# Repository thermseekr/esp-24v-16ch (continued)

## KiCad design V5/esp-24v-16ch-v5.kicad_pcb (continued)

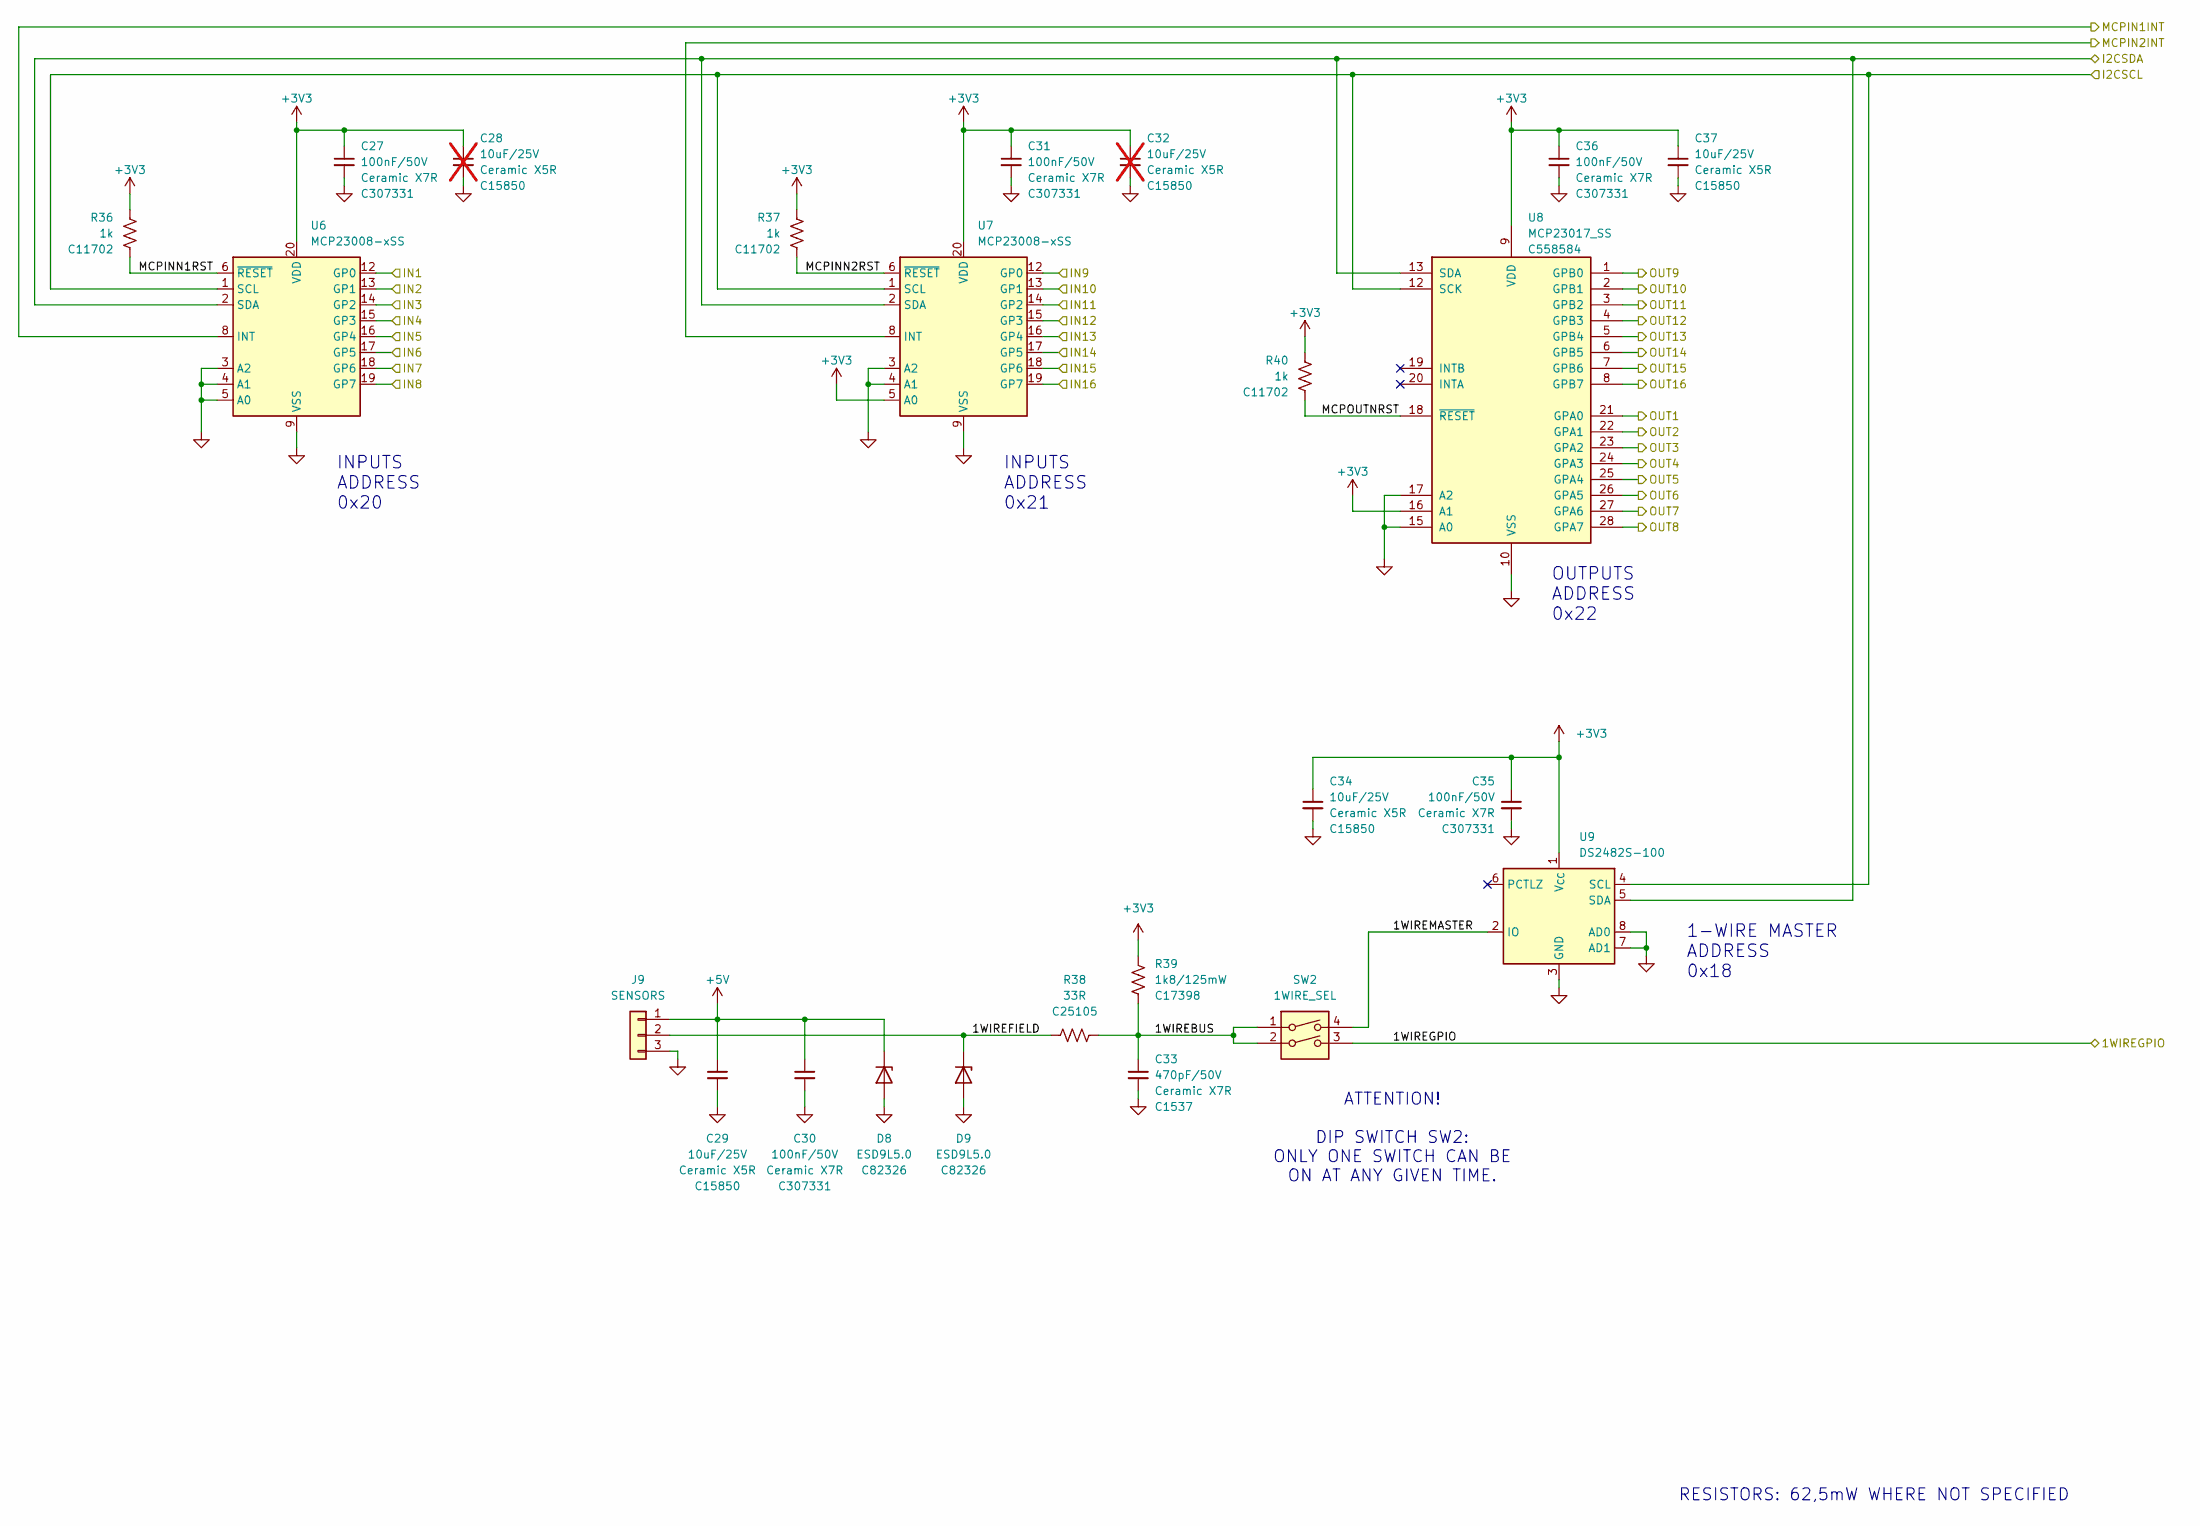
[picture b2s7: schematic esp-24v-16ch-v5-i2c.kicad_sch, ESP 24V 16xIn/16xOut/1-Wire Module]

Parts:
C27, C30, C31, C35, C36: 100nF/50V; C_0402_1005Metric; Mfr PN CL05B104KB54PNC; JLCPCB BOM 1
C28, C32: 10uF/25V; C_0805_2012Metric; Mfr PN CL21A106KAYNNNE; JLCPCB BOM 1; not fitted
C29, C34, C37: 10uF/25V; C_0805_2012Metric; Mfr PN CL21A106KAYNNNE; JLCPCB BOM 1
C33: 470pF/50V; C_0402_1005Metric; Mfr PN 0402B471K500NT; JLCPCB BOM 1
D8, D9: ESD9L5.0; D_SOD-923; Mfr PN ESD9L5.0ST5G; JLCPCB BOM 1
J9: SENSORS; TerminalBlock_Dibo_DB141V-2.54-3P_1x03_P2.54mm_Vertical; Mfr PN DB141V-2.54-3P-GN; JLCPCB BOM 1
R36, R37, R40: 1k; R_0402_1005Metric; Mfr PN 0402WGF1001TCE; LCSC Part # C11702
R38: 33R; R_0402_1005Metric; Mfr PN 0402WGF330JTCE; LCSC Part # C25105
R39: 1k8/125mW; R_0805_2012Metric; Mfr PN 0805W8F1801T5E; LCSC Part # C17398
SW2: 1WIRE_SEL; SW_DIP_SPSTx02_Slide_Copal_CHS-02B_W7.62mm_P1.27mm; Mfr PN DSHP02TS-S; JLCPCB BOM 1
U6, U7: MCP23008-xSS; SSOP-20_5.3x7.2mm_P0.65mm
U8: MCP23017_SS; SSOP-28_5.3x10.2mm_P0.65mm; Mfr PN MCP23017T-E/SS; JLCPCB BOM 1
U9: DS2482S-100; SO-8_3.9x4.9mm_P1.27mm; Mfr PN DS2482S-100; JLCPCB BOM 1

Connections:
+3V3: C27.1, C28.1, C31.1, C32.1, C34.1, C35.1, C36.1, C37.1, R36.1, R37.1, R39.1, R40.1, U6.20 (VDD), U7.5 (A0), U7.20 (VDD), U8.9 (VDD), U8.16 (A1), U9.1 (V_{CC}); also elsewhere on the board
+5V: C29.1, C30.1, D8.1 (K), J9.1; also elsewhere on the board
/I2C Devices/1WIREBUS: C33.1, R38.2, R39.2, SW2.1, SW2.2
/I2C Devices/1WIREFIELD: D9.1 (K), J9.2, R38.1
/I2C Devices/1WIREGPIO: SW2.3; also elsewhere on the board
/I2C Devices/1WIREMASTER: SW2.4, U9.2 (IO)
/I2C Devices/I2CSCL: U6.1 (SCL), U7.1 (SCL), U8.12 (SCK), U9.4 (SCL); also elsewhere on the board
/I2C Devices/I2CSDA: U6.2 (SDA), U7.2 (SDA), U8.13 (SDA), U9.5 (SDA); also elsewhere on the board
/I2C Devices/MCPIN1INT: U6.8 (INT); also elsewhere on the board
/I2C Devices/MCPIN2INT: U7.8 (INT); also elsewhere on the board
/I2C Devices/MCPINN1RST: R36.2, U6.6 (~RESET)
/I2C Devices/MCPINN2RST: R37.2, U7.6 (~RESET)
/I2C Devices/MCPOUTNRST: R40.2, U8.18 (~RESET)
/INPUT1: U6.12 (GP0); also elsewhere on the board
/INPUT2: U6.13 (GP1); also elsewhere on the board
/INPUT3: U6.14 (GP2); also elsewhere on the board
/INPUT4: U6.15 (GP3); also elsewhere on the board
/INPUT5: U6.16 (GP4); also elsewhere on the board
/INPUT6: U6.17 (GP5); also elsewhere on the board
/INPUT7: U6.18 (GP6); also elsewhere on the board
/INPUT8: U6.19 (GP7); also elsewhere on the board
/INPUT9: U7.12 (GP0); also elsewhere on the board
/INPUT10: U7.13 (GP1); also elsewhere on the board
/INPUT11: U7.14 (GP2); also elsewhere on the board
/INPUT12: U7.15 (GP3); also elsewhere on the board
/INPUT13: U7.16 (GP4); also elsewhere on the board
/INPUT14: U7.17 (GP5); also elsewhere on the board
/INPUT15: U7.18 (GP6); also elsewhere on the board
/INPUT16: U7.19 (GP7); also elsewhere on the board
/OUTPUT1: U8.21 (GPA0); also elsewhere on the board
/OUTPUT2: U8.22 (GPA1); also elsewhere on the board
/OUTPUT3: U8.23 (GPA2); also elsewhere on the board
/OUTPUT4: U8.24 (GPA3); also elsewhere on the board
/OUTPUT5: U8.25 (GPA4); also elsewhere on the board
/OUTPUT6: U8.26 (GPA5); also elsewhere on the board
/OUTPUT7: U8.27 (GPA6); also elsewhere on the board
/OUTPUT8: U8.28 (GPA7); also elsewhere on the board
/OUTPUT9: U8.1 (GPB0); also elsewhere on the board
/OUTPUT10: U8.2 (GPB1); also elsewhere on the board
/OUTPUT11: U8.3 (GPB2); also elsewhere on the board
/OUTPUT12: U8.4 (GPB3); also elsewhere on the board
/OUTPUT13: U8.5 (GPB4); also elsewhere on the board
/OUTPUT14: U8.6 (GPB5); also elsewhere on the board
/OUTPUT15: U8.7 (GPB6); also elsewhere on the board
/OUTPUT16: U8.8 (GPB7); also elsewhere on the board
GND: C27.2, C28.2, C29.2, C30.2, C31.2, C32.2, C33.2, C34.2, C35.2, C36.2, C37.2, D8.2 (A), D9.2 (A), J9.3, U6.3 (A2), U6.4 (A1), U6.5 (A0), U6.9 (VSS), U7.3 (A2), U7.4 (A1), U7.9 (VSS), U8.10 (VSS), U8.15 (A0), U8.17 (A2), U9.3 (GND), U9.7 (AD1), U9.8 (AD0); also elsewhere on the board

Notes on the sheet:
OUTPUTS ADDRESS 0x22
INPUTS ADDRESS 0x20
RESISTORS: 62,5mW WHERE NOT SPECIFIED
1-WIRE MASTER ADDRESS 0x18
INPUTS ADDRESS 0x21
ATTENTION! DIP SWITCH SW2: ONLY ONE SWITCH CAN BE ON AT ANY GIVEN TIME.

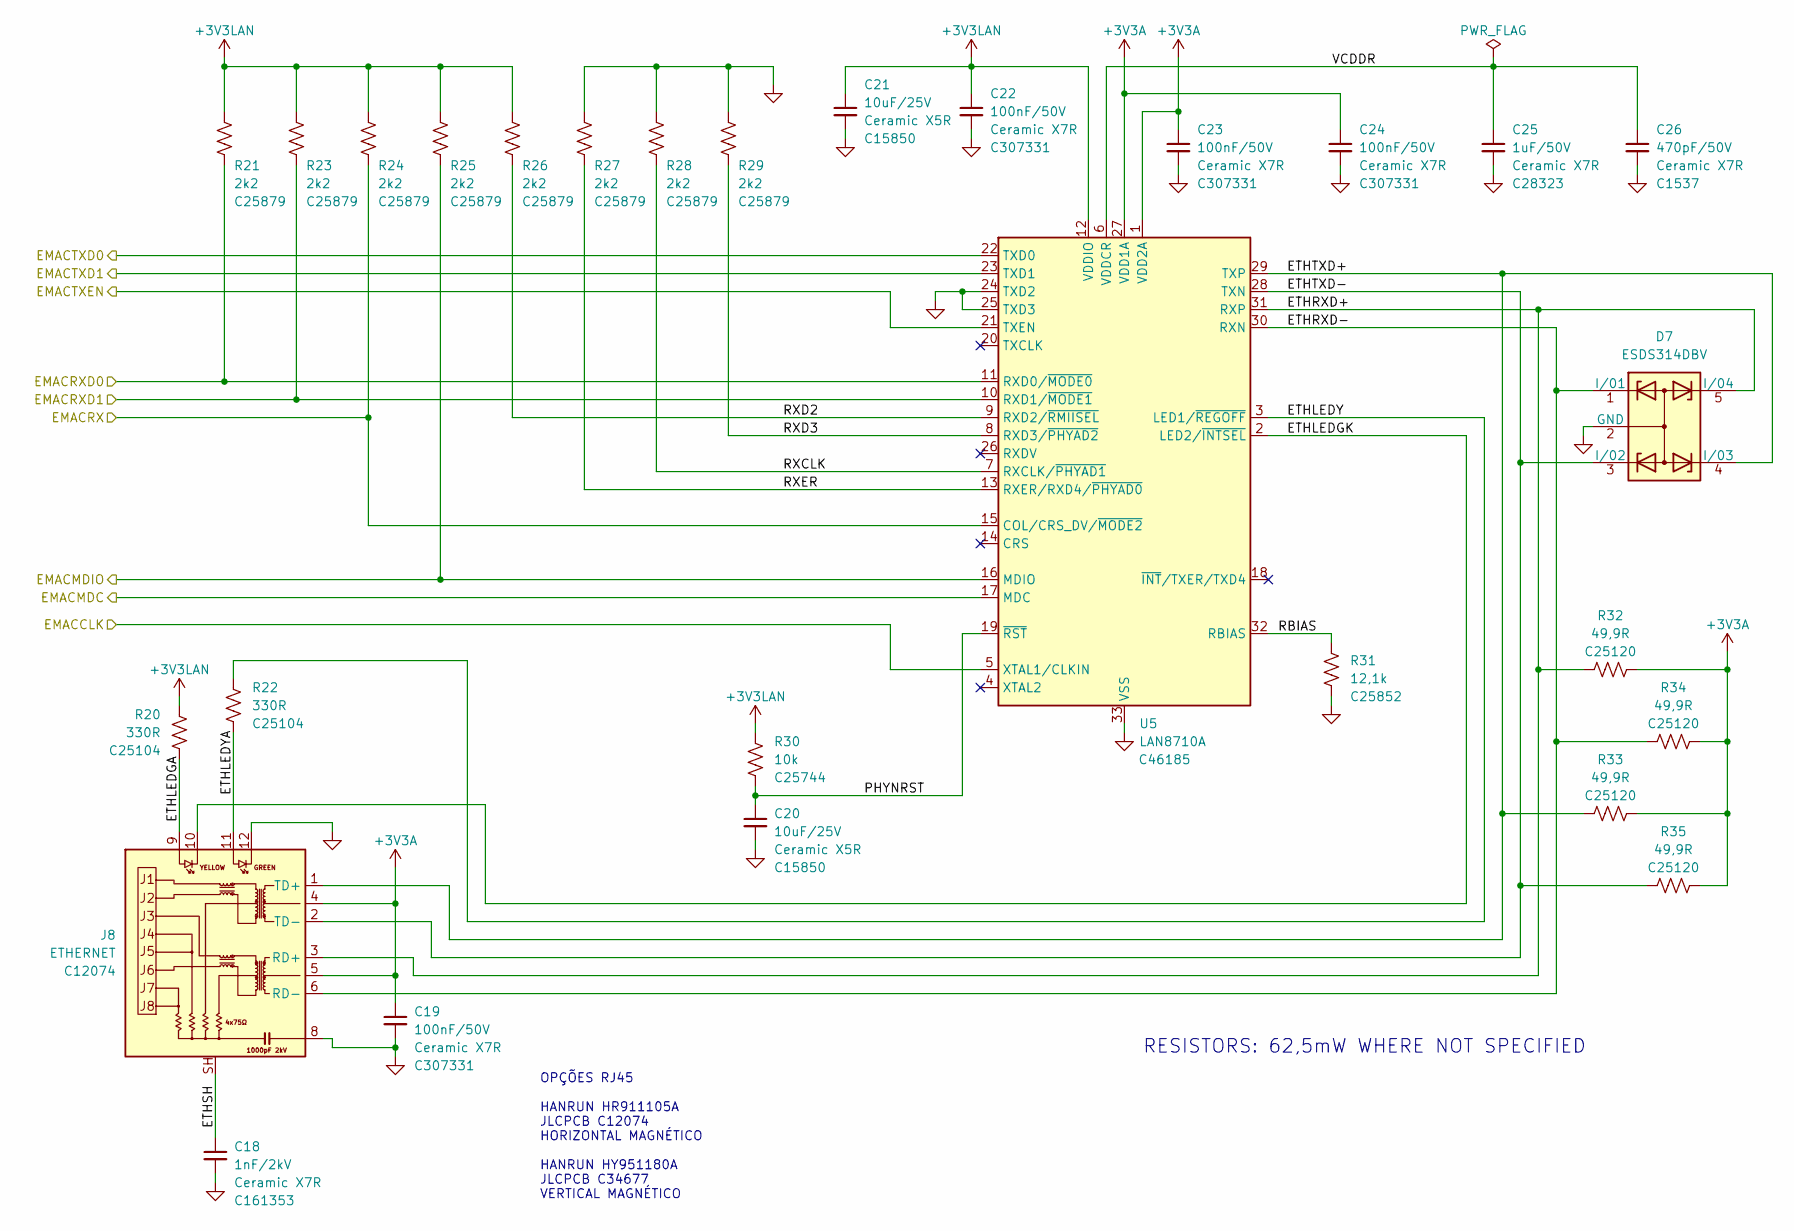
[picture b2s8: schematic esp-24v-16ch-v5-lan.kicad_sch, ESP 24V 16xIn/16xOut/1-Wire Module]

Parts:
C18: 1nF/2kV; C_1206_3216Metric; Mfr PN GR431BR7LA102KW66L; JLCPCB BOM 1
C19, C22, C23, C24: 100nF/50V; C_0402_1005Metric; Mfr PN CL05B104KB54PNC; JLCPCB BOM 1
C20, C21: 10uF/25V; C_0805_2012Metric; Mfr PN CL21A106KAYNNNE; JLCPCB BOM 1
C25: 1uF/50V; C_0805_2012Metric; Mfr PN CL21B105KBFNNNE; JLCPCB BOM 1
C26: 470pF/50V; C_0402_1005Metric; Mfr PN 0402B471K500NT; JLCPCB BOM 1
D7: ESDS314DBV; SOT-23-5; Mfr PN ESDS314DBVR; JLCPCB BOM 1
J8: ETHERNET; RJ45_HanRun_HR915340A; Mfr PN HR911105A; JLCPCB BOM 1
R20, R22: 330R; R_0402_1005Metric; Mfr PN 0402WGF3300TCE; LCSC Part # C25104
R21, R23, R24, R25, R26, R27, R28, R29: 2k2; R_0402_1005Metric; Mfr PN 0402WGF2201TCE; LCSC Part # C25879
R30: 10k; R_0402_1005Metric; Mfr PN 0402WGF1002TCE; LCSC Part # C25744
R31: 12,1k; R_0402_1005Metric; Mfr PN 0402WGF1212TCE; JLCPCB BOM 1
R32, R33, R34, R35: 49,9R; R_0402_1005Metric; Mfr PN 0402WGF499JTCE; JLCPCB BOM 1
U5: LAN8710A; QFN-32-1EP_5x5mm_P0.5mm_EP3.3x3.3mm_ThermalVias; Mfr PN LAN8710A-EZC-TR; JLCPCB BOM 1

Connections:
+3V3A: C19.1, C23.1, C24.1, J8.4, J8.5, R32.2, R33.2, R34.2, R35.2, U5.1 (VDD2A), U5.27 (VDD1A); also elsewhere on the board
+3V3LAN: C21.1, C22.1, R20.1, R21.1, R23.1, R24.1, R25.1, R26.1, R30.2, U5.12 (VDDIO); also elsewhere on the board
/LAN/EMACCLK: U5.5 (XTAL1/CLKIN); also elsewhere on the board
/LAN/EMACMDC: U5.17 (MDC); also elsewhere on the board
/LAN/EMACMDIO: R25.2, U5.16 (MDIO); also elsewhere on the board
/LAN/EMACRX: R24.2, U5.15 (COL/CRS_DV/~MODE2); also elsewhere on the board
/LAN/EMACRXD0: R21.2, U5.11 (RXD0/~MODE0); also elsewhere on the board
/LAN/EMACRXD1: R23.2, U5.10 (RXD1/~MODE1); also elsewhere on the board
/LAN/EMACTXD0: U5.22 (TXD0); also elsewhere on the board
/LAN/EMACTXD1: U5.23 (TXD1); also elsewhere on the board
/LAN/EMACTXEN: U5.21 (TXEN); also elsewhere on the board
/LAN/ETHLEDGA: J8.9, R20.2
/LAN/ETHLEDGK: J8.10, U5.2 (LED2/~INTSEL)
/LAN/ETHLEDY: R22.1, U5.3 (LED1/~REGOFF)
/LAN/ETHLEDYA: J8.11, R22.2
/LAN/ETHRXD+: D7.5 (I/04), J8.3 (RD+), R32.1, U5.31 (RXP)
/LAN/ETHRXD-: D7.1 (I/01), J8.6 (RD-), R34.1, U5.30 (RXN)
/LAN/ETHSH: C18.1, J8.SH
/LAN/ETHTXD+: D7.4 (I/03), J8.1 (TD+), R33.1, U5.29 (TXP)
/LAN/ETHTXD-: D7.3 (I/02), J8.2 (TD-), R35.1, U5.28 (TXN)
/LAN/PHYNRST: C20.1, R30.1, U5.19 (~RST)
/LAN/RBIAS: R31.1, U5.32 (RBIAS)
/LAN/RXCLK: R28.2, U5.7 (RXCLK/~PHYAD1)
/LAN/RXD2: R26.2, U5.9 (RXD2/~RMIISEL)
/LAN/RXD3: R29.2, U5.8 (RXD3/~PHYAD2)
/LAN/RXER: R27.2, U5.13 (RXER/RXD4/~PHYAD0)
/LAN/VCDDR: C25.1, C26.1, U5.6 (VDDCR)
GND: C18.2, C19.2, C20.2, C21.2, C22.2, C23.2, C24.2, C25.2, C26.2, D7.2 (GND), J8.8, J8.12, R27.1, R28.1, R29.1, R31.2, U5.24 (TXD2), U5.25 (TXD3), U5.33 (VSS); also elsewhere on the board

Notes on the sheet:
OPÇÕES RJ45 HANRUN HR911105A JLCPCB C12074 HORIZONTAL MAGNÉTICO HANRUN HY951180A JLCPCB C34677 VERTICAL MAGNÉTICO
RESISTORS: 62,5mW WHERE NOT SPECIFIED

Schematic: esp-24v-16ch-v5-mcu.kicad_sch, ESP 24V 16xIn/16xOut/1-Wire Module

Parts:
C13, C16: 10uF/25V; C_0805_2012Metric; Mfr PN CL21A106KAYNNNE; JLCPCB BOM 1
C14, C17: 100nF/50V; C_0402_1005Metric; Mfr PN CL05B104KB54PNC; JLCPCB BOM 1
C15: 1uF/50V; C_0805_2012Metric; Mfr PN CL21B105KBFNNNE; JLCPCB BOM 1
Q3: UMH3N; SOT-363_SC-70-6; Mfr PN UMH3N; JLCPCB BOM 1
R12, R13, R18: 10k; R_0402_1005Metric; Mfr PN 0402WGF1002TCE; LCSC Part # C25744
R14: 33R; R_0402_1005Metric; Mfr PN 0402WGF330JTCE; LCSC Part # C25105
R15, R16, R17, R19: 2k2; R_0402_1005Metric; Mfr PN 0402WGF2201TCE; LCSC Part # C25879
SW1: RESET; SW_SPST_Xunpu_TS1088AR02016; Mfr PN TS-1088-AR02016; JLCPCB BOM 1
U3: CH340K; SSOP-10-1EP_3.9x4.9mm_P1mm_EP2.1x3.3mm; Mfr PN CH340K; JLCPCB BOM 1
U4: ESP32-WROOM-32UE-N16; ESP32-WROOM-32U; Mfr PN ESP32-WROOM-32UE-N16; JLCPCB BOM 1

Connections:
+3V3: C13.1, C14.1, C16.1, C17.1, R12.1, R13.1, R15.1, R16.1, R17.1, R19.1, U3.7 (VCC), U3.10 (V3), U4.2 (VDD); also elsewhere on the board
/I2C Devices/1WIREGPIO: U4.27 (IO16); also elsewhere on the board
/I2C Devices/I2CSCL: R17.2, U4.8 (IO32); also elsewhere on the board
/I2C Devices/I2CSDA: R19.2, U4.9 (IO33); also elsewhere on the board
/I2C Devices/MCPIN1INT: R15.2, U4.16 (IO13); also elsewhere on the board
/I2C Devices/MCPIN2INT: R16.2, U4.13 (IO14); also elsewhere on the board
/LAN/EMACCLK: R14.2; also elsewhere on the board
/LAN/EMACMDC: U4.37 (IO23); also elsewhere on the board
/LAN/EMACMDIO: U4.30 (IO18); also elsewhere on the board
/LAN/EMACRX: U4.12 (IO27); also elsewhere on the board
/LAN/EMACRXD0: U4.10 (IO25); also elsewhere on the board
/LAN/EMACRXD1: U4.11 (IO26); also elsewhere on the board
/LAN/EMACTXD0: U4.31 (IO19); also elsewhere on the board
/LAN/EMACTXD1: U4.36 (IO22); also elsewhere on the board
/LAN/EMACTXEN: U4.33 (IO21); also elsewhere on the board
/MCU/ESPCLK: R14.1, U4.28 (IO17)
/MCU/ESPEN: C15.1, Q3.6 (C1), R12.2, SW1.2, U4.3 (EN)
/MCU/ESPPROG: Q3.3 (C2), R13.2, U4.25 (IO0)
/MCU/PHYPWR: R18.1, U4.14 (IO12); also elsewhere on the board
/MCU/UARTNDTR: Q3.2 (B1), Q3.4 (E2), U3.4 (~DTR)
/MCU/UARTNRTS: Q3.1 (E1), Q3.5 (B2), U3.6 (~RTS)
/MCU/UARTRXD: U3.9 (RXD), U4.35 (TXD0/IO1)
/MCU/UARTTXD: U3.8 (TXD), U4.34 (RXD0/IO3)
/MCU/USBD+: U3.1 (UD+); also elsewhere on the board
/MCU/USBD-: U3.2 (UD-); also elsewhere on the board
GND: C13.2, C14.2, C15.2, C16.2, C17.2, R18.2, SW1.1, U3.3 (GND), U3.11 (GND), U4.1 (GND), U4.15 (GND), U4.38 (GND), U4.39 (GND); also elsewhere on the board

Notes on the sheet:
TASMOTA CONFIGS The configs below must be applied via terminal/console and adjusted according to the desired hostname, device name, network addresses and behavior of switches. Configure switches: > backlog switchmode1 5; switchmode2 5; switchmode3 5; switchmode4 5; switchmode5 5; switchmode6 5; swi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
TEMPLATE FOR GPIO ASSIGNMENT {"NAME":"ESP-24V-16CH-V5","GPIO":[0,3200,0,3232,0,0,0,0,5536,10240,10241,0,0, 0,5600,0,0,0,0,5568,0,0,0,0,0,0,0,0,608,640,192,193,0,0,0,0],"FLAG":0,"BASE":1} See https://tasmota.github.io/docs/Templates/
TEMPLATE FOR MCP23017 I/O ASSIGNMENT {"NAME":"MCP23017 expander","BASE":0,"GPIO":[192,193,194,195,196,197,198,0,199,200,201, 202,203,204,205,0,224,225,226,227,228,229,230,231,232,233,234,235,236,237,238,239], "IOCON":0x5C} Save as mcp23x.dat and load into tasmota's filesystem. See https://tasmota.g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
RESISTORS: 62,5mW WHERE NOT SPECIFIED
ESP32 GPIO ASSIGNMENT PIN PORT FUNCTION COMPONENT 25 GPIO0 AUTO FLASH MODE 0 35 GPIO1 SERIAL TX 3200 24 GPIO2 - 0 34 GPIO3 SERIAL RX 3232 26 GPIO4 - 0 29 GPIO5 - 0 17 GPIO9 - 0 18 GPIO10 - 0 14 GPIO12 ETH POWER 5536 16 GPIO13 MCP23017 INT1 10240 13 GPIO14 MCP23017 INT2 10241 23 GPIO15 - 0 27 GPIO16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

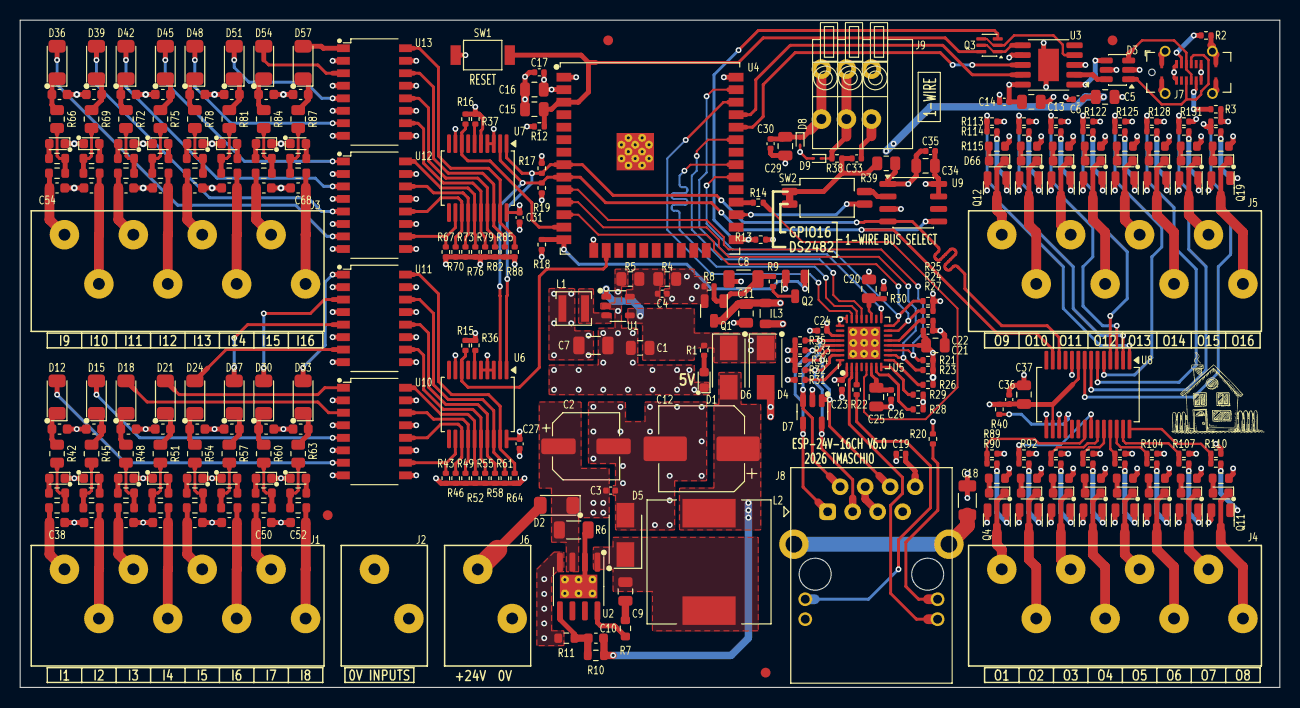
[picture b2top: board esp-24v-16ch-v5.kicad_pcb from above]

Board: 4 copper layers, 128.0 x 67.8 mm, 327 parts (0 on the bottom side), 230 nets.

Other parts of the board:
Ref**: Val**; Grandmas_small_silk

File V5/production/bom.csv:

Designator,Footprint,Quantity,Value,LCSC Part #
"C1, C11, C13, C16, C20, C21, C29, C34, C37",0805,9,10uF/25V,C15850
C10,0603,1,12pF/50V,C38523
C12,CP_Elec_8x10.5,1,470uF/16V,C96179
"C14, C17, C19, C22, C23, C24, C27, C3, C30, C31, C35, C36, C6",0402,13,100nF/50V,C307331
"C15, C25, C5",0805,3,1uF/50V,C28323
C18,1206,1,1nF/2kV,C161353
C2,CP_Elec_6.3x5.4,1,47uF/35V,C129415
"C26, C33",0402,2,470pF/50V,C1537
"C38, C40, C42, C44, C46, C48, C50, C52, C54, C56, C58, C60, C62, C64, C66, C68",0603,16,1nF/50V,C1588
"C39, C41, C43, C45, C47, C49, C51, C53, C55, C57, C59, C61, C63, C65, C67, C69",0603,16,33nF/50V,C21117
C4,0402,1,22pF/50V,C1555
"C7, C8",1206,2,22uF/10V,C5672
C9,0805,1,100nF/100V,C28233
"D1, D11, D14, D17, D20, D23, D26, D29, D32, D35, D38, D41, D44, D47, D50, D53, D56, D58, D59, D60, D61, D62, D63, D64, D65, D66, D67, D68, D69, D70, D71, D72, D73",0603,33,WHITE/0603,C2290
"D12, D15, D18, D21, D24, D27, D30, D33, D36, D39, D42, D45, D48, D51, D54, D57",D_SOD-123,16,9V1/500mW,C19077407
D2,D_SOD-123,1,SM4007PL,C64898
D3,SOT-23-6,1,USBLC6-2SC6,C7519
"D4, D6",D_SMA,2,SS34,C8678
D5,D_SMA,1,SS510,C65010
D7,SOT-23-5,1,ESDS314DBV,C1847859
"D8, D9",D_SOD-923,2,ESD9L5.0,C82326
"FB1, FB10, FB11, FB12, FB13, FB14, FB15, FB16, FB2, FB3, FB4, FB5, FB6, FB7, FB8, FB9",0603,16,600R/100MHz,C85833
"J1, J3, J4, J5",TerminalBlock_Dibo_DB141V-2.54-8P_1x08_P2.54mm_Vertical,4,DB141V-2.54-8P,C2898750
J2,TerminalBlock_Wago_250-202_1x02_P3.5mm_45Degree,1,GNDIO,C2765061
J6,TerminalBlock_Wago_250-202_1x02_P3.5mm_45Degree,1,VIN,C2765061
J7,USB_C_Receptacle_ShouHan_TYPE-C-16PLT-H10.0,1,USB_C_Receptacle_USB2.0,C3151749
J8,RJ45_HanRun_HR915340A,1,ETHERNET,C12074
J9,TerminalBlock_Dibo_DB141V-2.54-3P_1x03_P2.54mm_Vertical,1,SENSORS,C2898745
L1,L_3x3mm_h1.5mm,1,"2,2uH 1,5A",C370424
L2,L_12x12mm_h6mm,1,"33uH 2,1A",C169386
L3,0805,1,2A 600R,C139168
Q1,SOT-23,1,WPM2015-3/TR,C558305
"Q10, Q11, Q12, Q13, Q14, Q15, Q16, Q17, Q18, Q19, Q4, Q5, Q6, Q7, Q8, Q9",SOT-23-Narrow,16,MMBT2222A,C8512
Q2,SOT-23,1,MMUN2211LT3G,C150229
Q3,SOT-363_SC-70-6,1,UMH3N,C62892
"R1, R102, R105, R108, R111, R114, R117, R120, R123, R126, R129, R132, R135, R36, R37, R40, R9, R90, R93, R96, R99",0402,21,1k,C11702
R10,0603,1,300k/100mW,C23024
"R100, R103, R106, R109, R112, R115, R118, R121, R124, R127, R130, R133, R136, R41, R44, R47, R50, R53, R56, R59, R62, R65, R68, R71, R74, R77, R80, R83, R86, R91, R94, R97",0603,32,10k/100mW,C25804
"R101, R104, R107, R110, R113, R116, R119, R12, R122, R125, R128, R13, R131, R134, R18, R30, R8, R89, R92, R95, R98",0402,21,10k,C25744
R11,0603,1,"52,3k/100mW",C185323
"R14, R38",0402,2,33R,C25105
"R15, R16, R17, R19, R21, R23, R24, R25, R26, R27, R28, R29, R43, R46, R49, R52, R55, R58, R61, R64, R67, R70, R73, R76, R79, R82, R85, R88",0402,28,2k2,C25879
"R2, R3",0402,2,"5,1k",C105872
"R20, R22",0402,2,330R,C25104
R31,0402,1,"12,1k",C25852
"R32, R33, R34, R35",0402,4,"49,9R",C25120
"R39, R42, R45, R48, R51, R54, R57, R60, R63, R66, R69, R72, R75, R78, R81, R84, R87",0805,17,1k8/125mW,C17398
R4,0805,1,100k/125mW,C149504
R5,0805,1,"22,1k/125mW",C17552
R6,1206,1,30mR/333mW,C473665
R7,0603,1,"5,1R/100mW",C25197
SW1,SW_SPST_Xunpu_TS1088AR02016,1,RESET,C720477
SW2,SW_DIP_SPSTx02_Slide_Copal_CHS-02B_W7.62mm_P1.27mm,1,1WIRE_SEL,C319052
U1,SOT-23-5_Shorter_Pins,1,SY8089A1AAC,C479074
"U10, U11, U12, U13",SOP-16_4.4x10.4mm_P1.27mm,4,OR-3H7-4,C2838427
U2,SOIC-8-1EP_3.9x4.9mm_P1.27mm_EP2.41x3.81mm_ThermalVias,1,TX4138,C329267
U3,SSOP-10-1EP_3.9x4.9mm_P1mm_EP2.1x3.3mm,1,CH340K,C968586
U4,ESP32-WROOM-32U,1,ESP32-WROOM-32UE-N16,C701346
U5,QFN-32-1EP_5x5mm_P0.5mm_EP3.3x3.3mm_ThermalVias,1,LAN8710A,C46185
"U6, U7",SSOP-20_5.3x7.2mm_P0.65mm,2,MCP23008-xSS,
U8,SSOP-28_5.3x10.2mm_P0.65mm,1,MCP23017_SS,C558584
U9,SO-8_3.9x4.9mm_P1.27mm,1,DS2482S-100,C143306
